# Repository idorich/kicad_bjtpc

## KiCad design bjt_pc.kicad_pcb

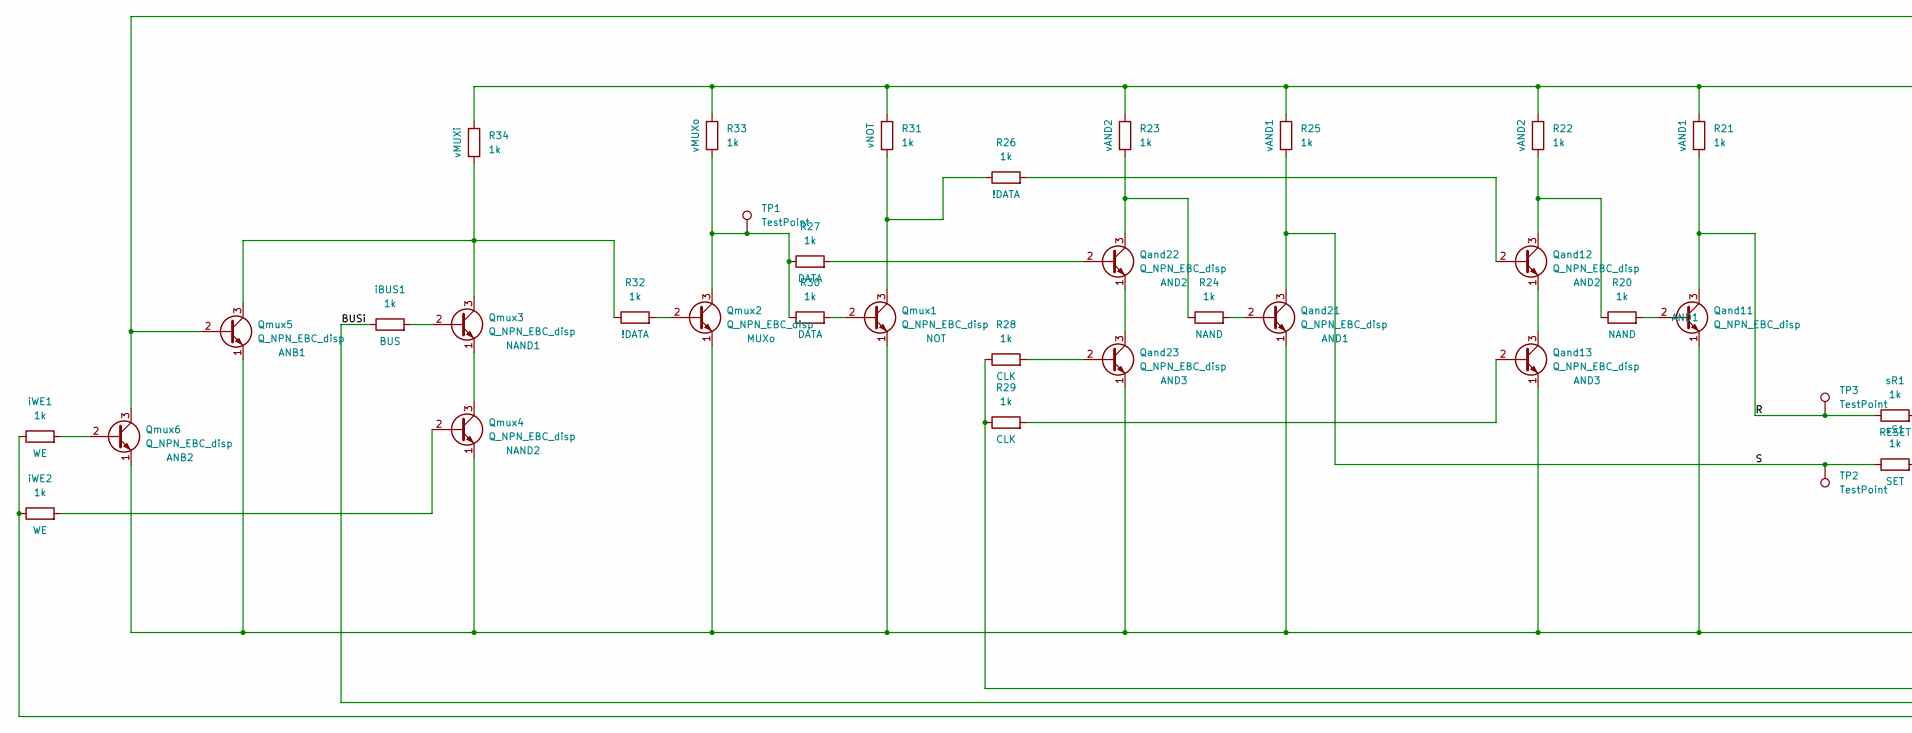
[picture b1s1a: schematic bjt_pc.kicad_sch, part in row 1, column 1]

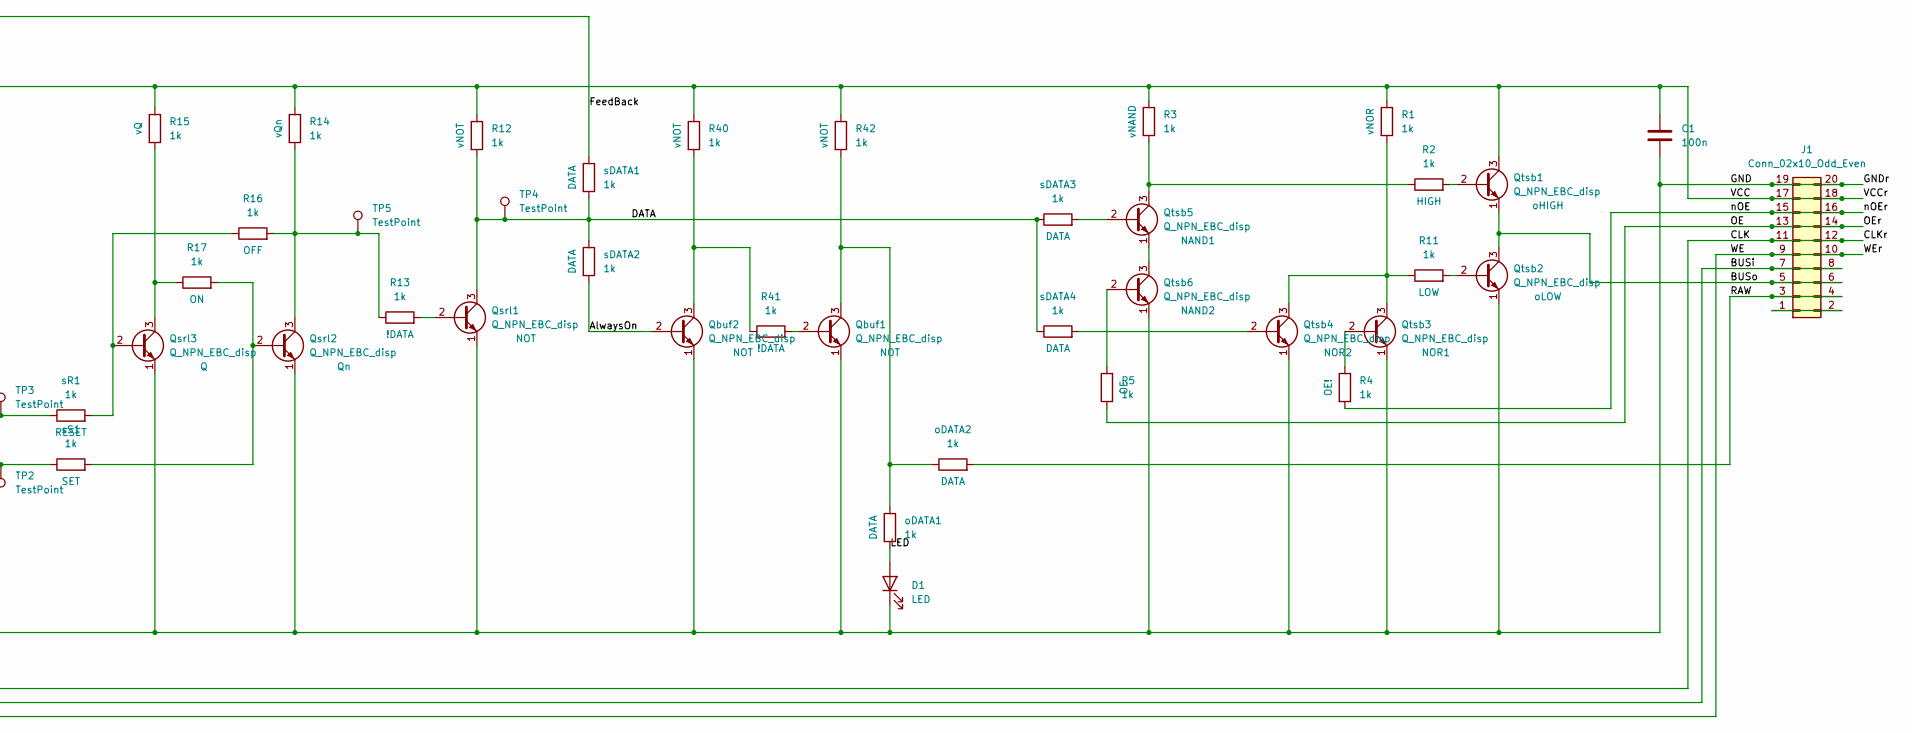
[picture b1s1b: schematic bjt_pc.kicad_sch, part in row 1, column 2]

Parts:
C1: 100n; C_Disc_D5.0mm_W2.5mm_P5.00mm
D1: LED; LED_D5.0mm
J1: Conn_02x10_Odd_Even; PinSocket_2x10_P2.54mm_Horizontal
Qand11, Qand12, Qand13, Qand21, Qand22, Qand23: Q_NPN_EBC_disp; TO-92_Inline_Wide
Qbuf1, Qbuf2: Q_NPN_EBC_disp; TO-92_Inline_Wide
Qmux1, Qmux2, Qmux3, Qmux4, Qmux5, Qmux6: Q_NPN_EBC_disp; TO-92_Inline_Wide
Qsrl1, Qsrl2, Qsrl3: Q_NPN_EBC_disp; TO-92_Inline_Wide
Qtsb1, Qtsb2, Qtsb3, Qtsb4, Qtsb5, Qtsb6: Q_NPN_EBC_disp; TO-92_Inline_Wide
R1, R2, R3, R4, R5, R11, R12, R13, R14, R15, R16, R17, R20, R21, R22, R23, R24, R25, R26, R27, R28, R29, R30, R31, R32, R33, R34, R40, R41, R42: 1k; R_Axial_DIN0207_L6.3mm_D2.5mm_P7.62mm_Horizontal_disp
TP1, TP2, TP3, TP4, TP5: TestPoint; TestPoint_THTPad_D3.0mm_Drill1.5mm
iBUS1: 1k; R_Axial_DIN0207_L6.3mm_D2.5mm_P7.62mm_Horizontal_disp
iWE1, iWE2: 1k; R_Axial_DIN0207_L6.3mm_D2.5mm_P7.62mm_Horizontal_disp
oDATA1, oDATA2: 1k; R_Axial_DIN0207_L6.3mm_D2.5mm_P7.62mm_Horizontal_disp
sDATA1, sDATA2, sDATA3, sDATA4: 1k; R_Axial_DIN0207_L6.3mm_D2.5mm_P7.62mm_Horizontal_disp
sR1: 1k; R_Axial_DIN0207_L6.3mm_D2.5mm_P7.62mm_Horizontal_disp
sS1: 1k; R_Axial_DIN0207_L6.3mm_D2.5mm_P7.62mm_Horizontal_disp

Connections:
/AlwaysOn: Qbuf2.2 (B), sDATA2.2
/BUSi: J1.7, J1.8, iBUS1.1
/BUSo: J1.5, J1.6, Qtsb1.1 (E), Qtsb2.3 (C)
/CLK: J1.11, J1.12, R28.1, R29.1
/DATA: Qsrl1.3 (C), R12.2, TP4.1, sDATA1.2, sDATA2.1, sDATA3.1, sDATA4.1
/FeedBack: Qmux5.2 (B), Qmux6.3 (C), sDATA1.1
/GND: C1.2, D1.1 (K), J1.19, J1.20, Qand11.1 (E), Qand13.1 (E), Qand21.1 (E), Qand23.1 (E), Qbuf1.1 (E), Qbuf2.1 (E), Qmux1.1 (E), Qmux2.1 (E), Qmux4.1 (E), Qmux5.1 (E), Qmux6.1 (E), Qsrl1.1 (E), Qsrl2.1 (E), Qsrl3.1 (E), Qtsb2.1 (E), Qtsb3.1 (E), Qtsb4.1 (E), Qtsb6.1 (E); also elsewhere on the board
/LED: D1.2 (A), oDATA1.2
/OE: J1.13, J1.14, R5.1
/R: Qand11.3 (C), R21.2, TP3.1, sR1.1
/RAW: J1.3, J1.4, oDATA2.2
/S: Qand21.3 (C), R25.2, TP2.1, sS1.1
/VCC: C1.1, J1.17, J1.18, Qtsb1.3 (C), R1.1, R3.1, R12.1, R14.1, R15.1, R21.1, R22.1, R23.1, R25.1, R31.1, R33.1, R34.1, R40.1, R42.1; also elsewhere on the board
/WE: J1.9, J1.10, iWE1.1, iWE2.1
/nOE: J1.15, J1.16, R4.2
unnamed: J1.1, J1.2
unnamed: Qand11.2 (B), R20.2
unnamed: Qand12.2 (B), R26.2
unnamed: Qand12.3 (C), R20.1, R22.2
unnamed: Qand12.1 (E), Qand13.3 (C)
unnamed: Qand13.2 (B), R29.2
unnamed: Qand21.2 (B), R24.2
unnamed: Qand22.2 (B), R27.2
unnamed: Qand22.3 (C), R23.2, R24.1
unnamed: Qand22.1 (E), Qand23.3 (C)
unnamed: Qand23.2 (B), R28.2
unnamed: Qbuf1.2 (B), R41.2
unnamed: Qbuf1.3 (C), R42.2, oDATA1.1, oDATA2.1
unnamed: Qbuf2.3 (C), R40.2, R41.1
unnamed: Qmux1.2 (B), R30.2
unnamed: Qmux1.3 (C), R26.1, R31.2
unnamed: Qmux2.2 (B), R32.2
unnamed: Qmux2.3 (C), R27.1, R30.1, R33.2, TP1.1
unnamed: Qmux3.2 (B), iBUS1.2
unnamed: Qmux3.3 (C), Qmux5.3 (C), R32.1, R34.2
unnamed: Qmux3.1 (E), Qmux4.3 (C)
unnamed: Qmux4.2 (B), iWE2.2
unnamed: Qmux6.2 (B), iWE1.2
unnamed: Qsrl1.2 (B), R13.2
unnamed: Qsrl2.2 (B), R17.2, sS1.2
unnamed: Qsrl2.3 (C), R13.1, R14.2, R16.2, TP5.1
unnamed: Qsrl3.2 (B), R16.1, sR1.2
unnamed: Qsrl3.3 (C), R15.2, R17.1
unnamed: Qtsb1.2 (B), R2.2
unnamed: Qtsb2.2 (B), R11.2
unnamed: Qtsb3.2 (B), R4.1
unnamed: Qtsb3.3 (C), Qtsb4.3 (C), R1.2, R11.1
unnamed: Qtsb4.2 (B), sDATA4.2
unnamed: Qtsb5.2 (B), sDATA3.2
unnamed: Qtsb5.3 (C), R2.1, R3.2
unnamed: Qtsb5.1 (E), Qtsb6.3 (C)
unnamed: Qtsb6.2 (B), R5.2

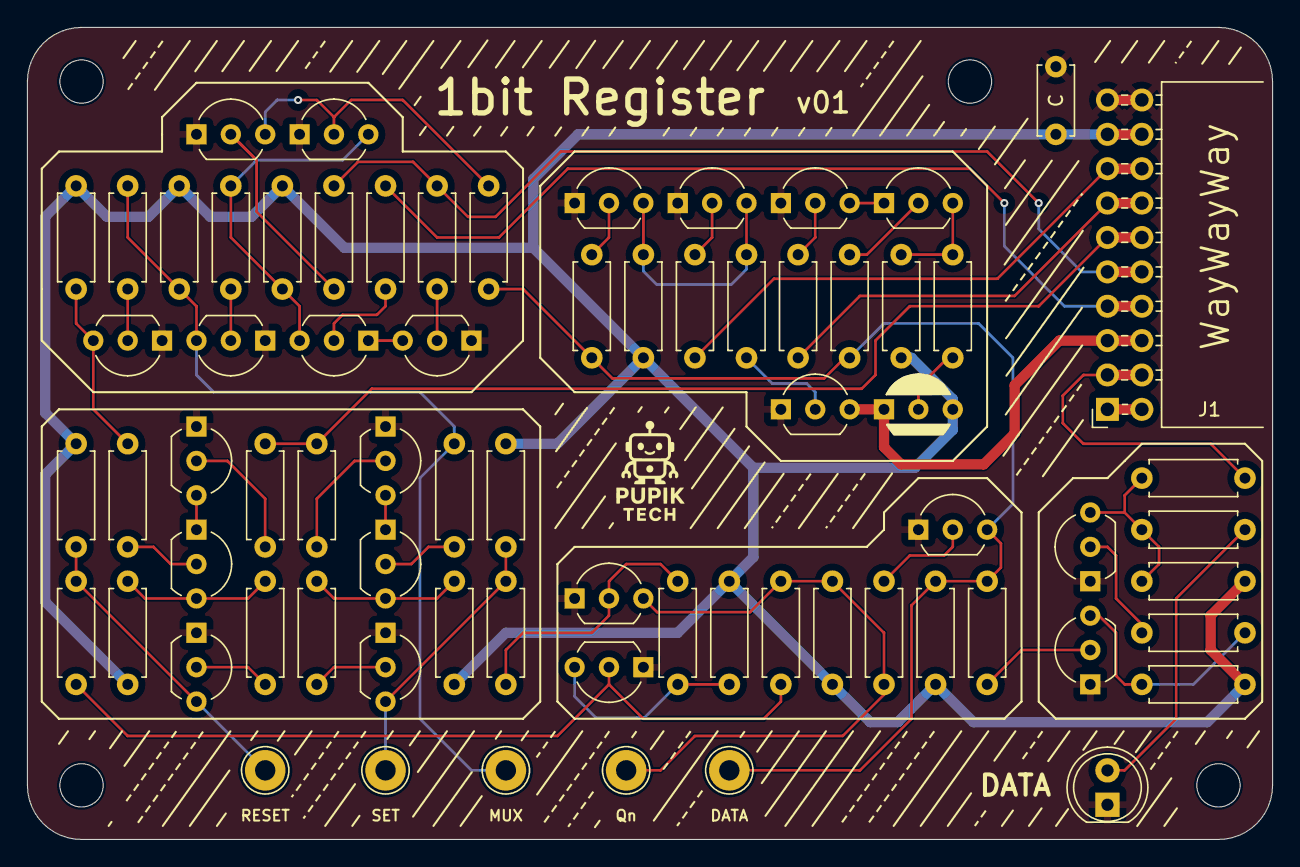
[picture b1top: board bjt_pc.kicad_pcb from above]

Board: 2 copper layers, 92.0 x 60.0 mm, 72 parts (0 on the bottom side), 52 nets.

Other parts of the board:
C: 100n; C_Disc_D5.0mm_W2.5mm_P5.00mm

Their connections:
/GND: C.2; also elsewhere on the board
/VCC: C.1; also elsewhere on the board

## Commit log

2025-06-26 Finalized compressed 1.0
2025-06-26 Added Test Points
2025-06-26 Added back silkscreen stuff
2025-06-26 cleanup commit
2025-06-26 cleanup commit pre-purchase
